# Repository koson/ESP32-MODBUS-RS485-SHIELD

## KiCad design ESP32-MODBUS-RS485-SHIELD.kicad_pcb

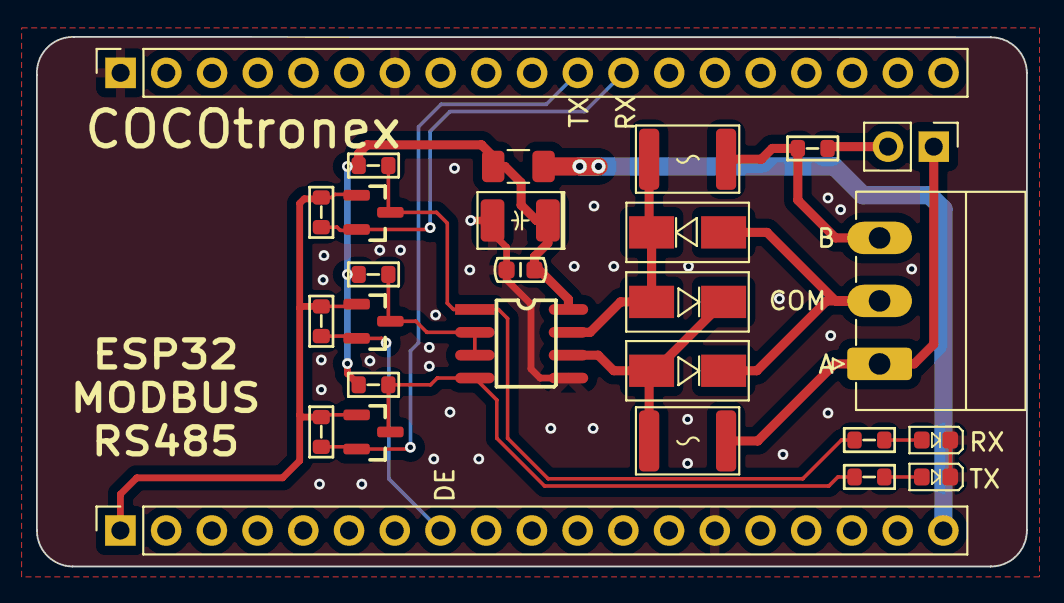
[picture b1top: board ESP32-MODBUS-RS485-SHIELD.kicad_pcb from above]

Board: 2 copper layers, 55.0 x 29.4 mm, 27 parts (0 on the bottom side), 18 nets.

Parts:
C3: 100nF; C_0603_1608Metric
C5: 10uF; CP_EIA-3528-21_Kemet-B
D33, D34, D35: SMAJ6.5CA; D_SMA
D36: GREEN; LED_0603_1608Metric
D37: RED; LED_0603_1608Metric
F1, F2: MF-MSMF050-2; Fuse_1812_4532Metric
F3: Polyfuse_Small; Fuse_1206_3216Metric
J1, J2: Conn_01x19; PinSocket_1x19_P2.54mm_Vertical
J9: RS485; PhoenixContact_MC_1,5_3-G-3.5_1x03_P3.50mm_Horizontal
J10: Conn_01x02; PinHeader_1x02_P2.54mm_Vertical
Q17, Q18, Q19: WST3400S; SOT-23
R36: 120; R_0603_1608Metric
R38, R39, R40, R41, R42, R43: 10k; R_0603_1608Metric
R45, R47: 470R; R_0603_1608Metric
U11: SN75176AD; SO08

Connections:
/3V3: J1.1, Q17.1 (G), Q18.1 (G), Q19.1 (G), R39.1, R41.1, R43.1
/5V: C3.1, C5.1, F3.2, R38.1, R40.1, R42.1, U11.8 (VCC)
/A: F2.2, J9.1, J10.1
/B: F1.2, J9.3, R36.1
/DE_5V: Q19.3 (D), R42.2, U11.2 (~RE), U11.3 (DE)
/D_5V: Q17.3 (D), R38.2, R45.1, U11.4 (D)
/RS485_COM: D34.1 (A1), D35.2 (A2), J9.2
/RS485_DE: J1.8, Q19.2 (S), R43.2
/RS485_RX: J2.12, Q18.2 (S), R41.2
/RS485_TX: J2.11, Q17.2 (S), R39.2
/R_5V: Q18.3 (D), R40.2, R47.1, U11.1 (R)
GND: C3.2, C5.2, D36.1 (K), D37.1 (K), J1.14, J2.1, J2.7, U11.5 (GND)
unnamed: D33.1 (A1), D34.2 (A2), F2.1, U11.6 (A)
unnamed: D33.2 (A2), D35.1 (A1), F1.1, U11.7 (B)
unnamed: D36.2 (A), R45.2
unnamed: D37.2 (A), R47.2
unnamed: F3.1, J1.19
unnamed: J10.2, R36.2

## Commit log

2023-01-21 add gerber files
